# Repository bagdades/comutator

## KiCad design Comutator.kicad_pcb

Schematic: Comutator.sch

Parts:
C1, C2: 1u; C_0805_2012Metric
D1: BAV99; SOT-23
D2: BZG05C9V1; D_MiniMELF
D3: LED; LED_D3.0mm
J1: Conn_01x03; PinHeader_1x03_P2.54mm_Vertical
J2: Conn_01x02; mors_2p
K1: FINDER-40.52; Relay_DPDT_Finder_40.52
Q1, Q2: IRLML2402; TSOT-23
Q3: BT139-600; TO-220-3_Horizontal_TabDown
R1, R4: 1k; R_0805_2012Metric
R2, R3: 100k; R_0805_2012Metric
R5: 510; R_0805_2012Metric
R6, R7: 360; R_1206_3216Metric
U1: MOC3063M; DIP-6_W7.62mm

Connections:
+5V: D2.1, D3.2, J1.1, K1.A1, R5.1
GND: C1.2, C2.2, J1.3, Q1.2, Q2.2
unnamed: C1.1, D1.1, Q1.1, R2.1
unnamed: C2.1, D1.2, Q2.1, R3.1
unnamed: D1.3, R1.1, R2.2, R3.2
unnamed: D2.2, K1.A2, Q1.3, R4.2
unnamed: D3.1, R4.1
unnamed: J1.2, R1.2
unnamed: J2.1, K1.14, K1.24, Q3.1 (A1), R7.1
unnamed: J2.2, K1.11, K1.21, Q3.2 (A2), R6.1
unnamed: K1.12, K1.22
unnamed: Q2.3, U1.2
unnamed: Q3.3 (G), R7.2, U1.4
unnamed: R5.2, U1.1
unnamed: R6.2, U1.6

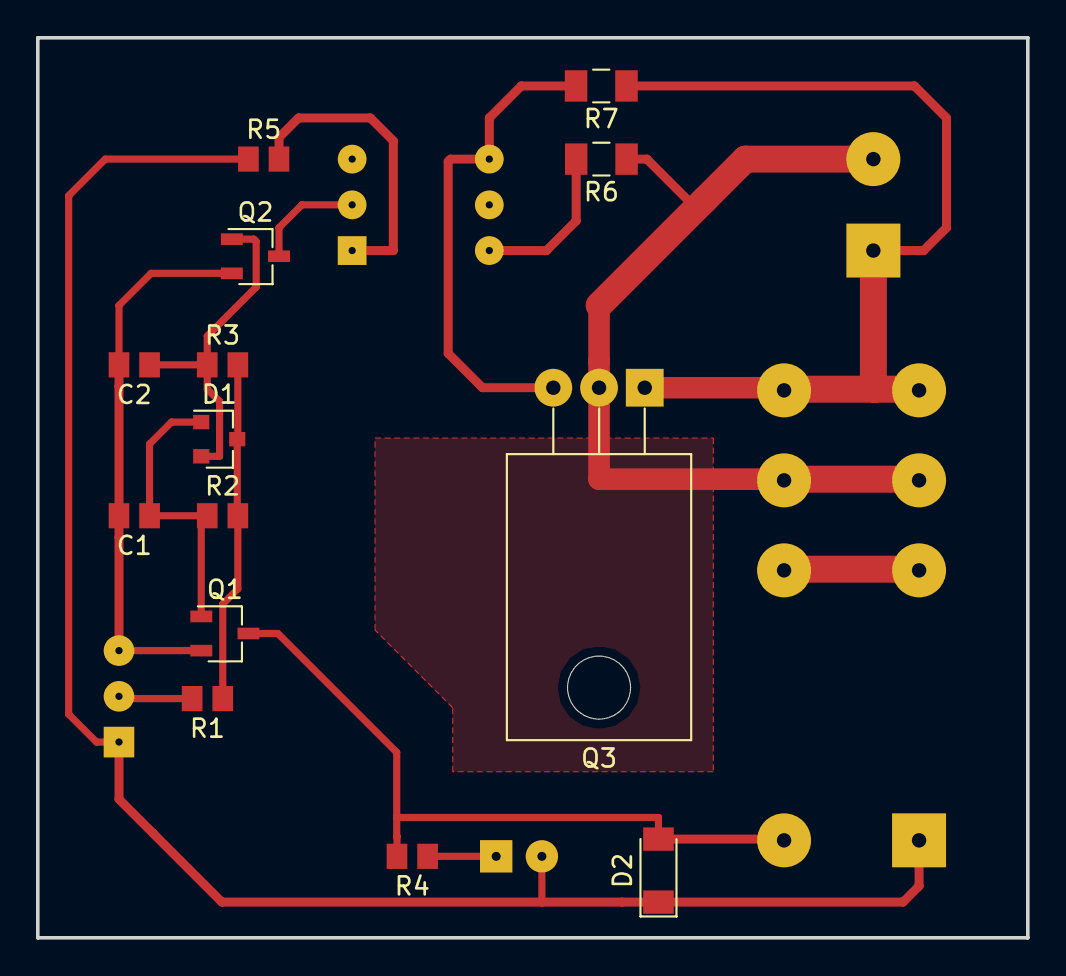
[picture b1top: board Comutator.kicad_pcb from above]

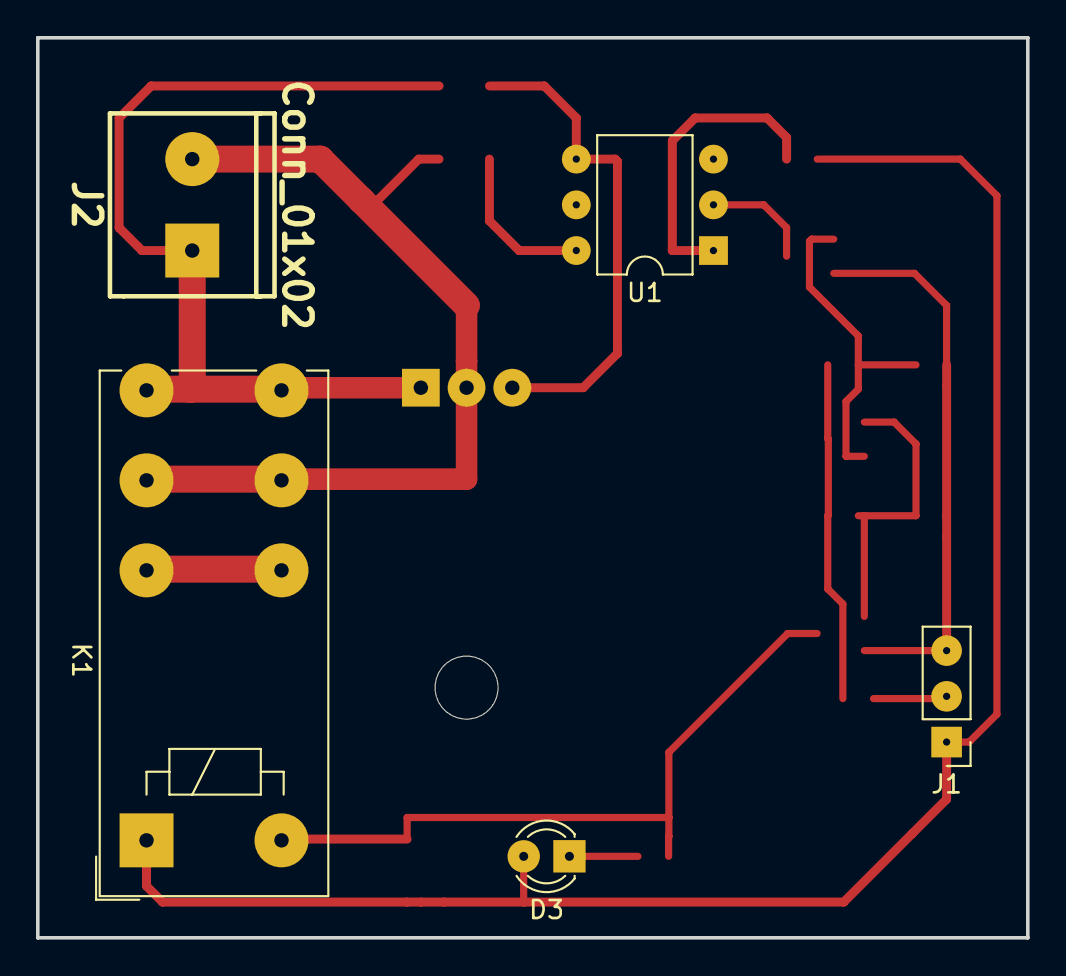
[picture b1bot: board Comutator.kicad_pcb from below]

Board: 2 copper layers, 55.0 x 50.0 mm, 19 parts (5 on the bottom side), 15 nets.

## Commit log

2018-06-15 Add input connector
2018-06-15 Add SO-6 package
2018-06-17 Create pcb
2018-06-18 Chage drill diameter on DIP8
